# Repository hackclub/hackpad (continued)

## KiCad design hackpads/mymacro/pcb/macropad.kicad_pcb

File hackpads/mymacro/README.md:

# HackPad
## My experience
As part of **Hack Club’s HACKPAD YSWS** program, I embarked on a rewarding journey to build my own DIY macropad. This experience allowed me to explore various technical disciplines, from designing a custom **PCB in KiCAD** to **coding my very own firmware with QMK**. The most challenging aspect of the project was undoubtedly the PCB design. It required extensive research into component specifications, navigating datasheets, and ensuring that each part—switches, diodes, microcontrollers—was properly integrated into the design. The process of **placing components and routing the traces** was the most time-consuming and working through these challenges gave me a much deeper understanding of electronics design.

On the other hand, the part I enjoyed the most was **working with CAD**. With my existing CAD skills, I was able to confidently create a functional layout for the macropad’s physical structure. Translating these skills into real-world applications for a product I could use was fulfilling and rewarding. Coding the firmware was surprisingly straightforward, thanks to QMK's user-friendly environment, making the software side of things much simpler than anticipated. 
***Overall, this project was an invaluable learning experience that not only introduced me to PCB design but also allowed me to merge my existing skills with new knowledge to create something functional.***
## Bill Of Materials

    Xiao RP2040
    PCF8574 IO expander
    SSD1306 0.96 OLED
    (2) 4.7k resistor
    (16) SK6812 LED
    (16) 1N4148 diodes
    (16) Cherry MX brown switches

    (16) any keycaps at hq
    (16) Mill-Max 0305s hotswap socket
    (2) any encoder knobs at hq
    (2) EC11 encoder with click function
    
    **--> Please laser cut the plate in 3mm clear acrylic and 3D print the rest of the pieces.**

### My Model

### My schematic

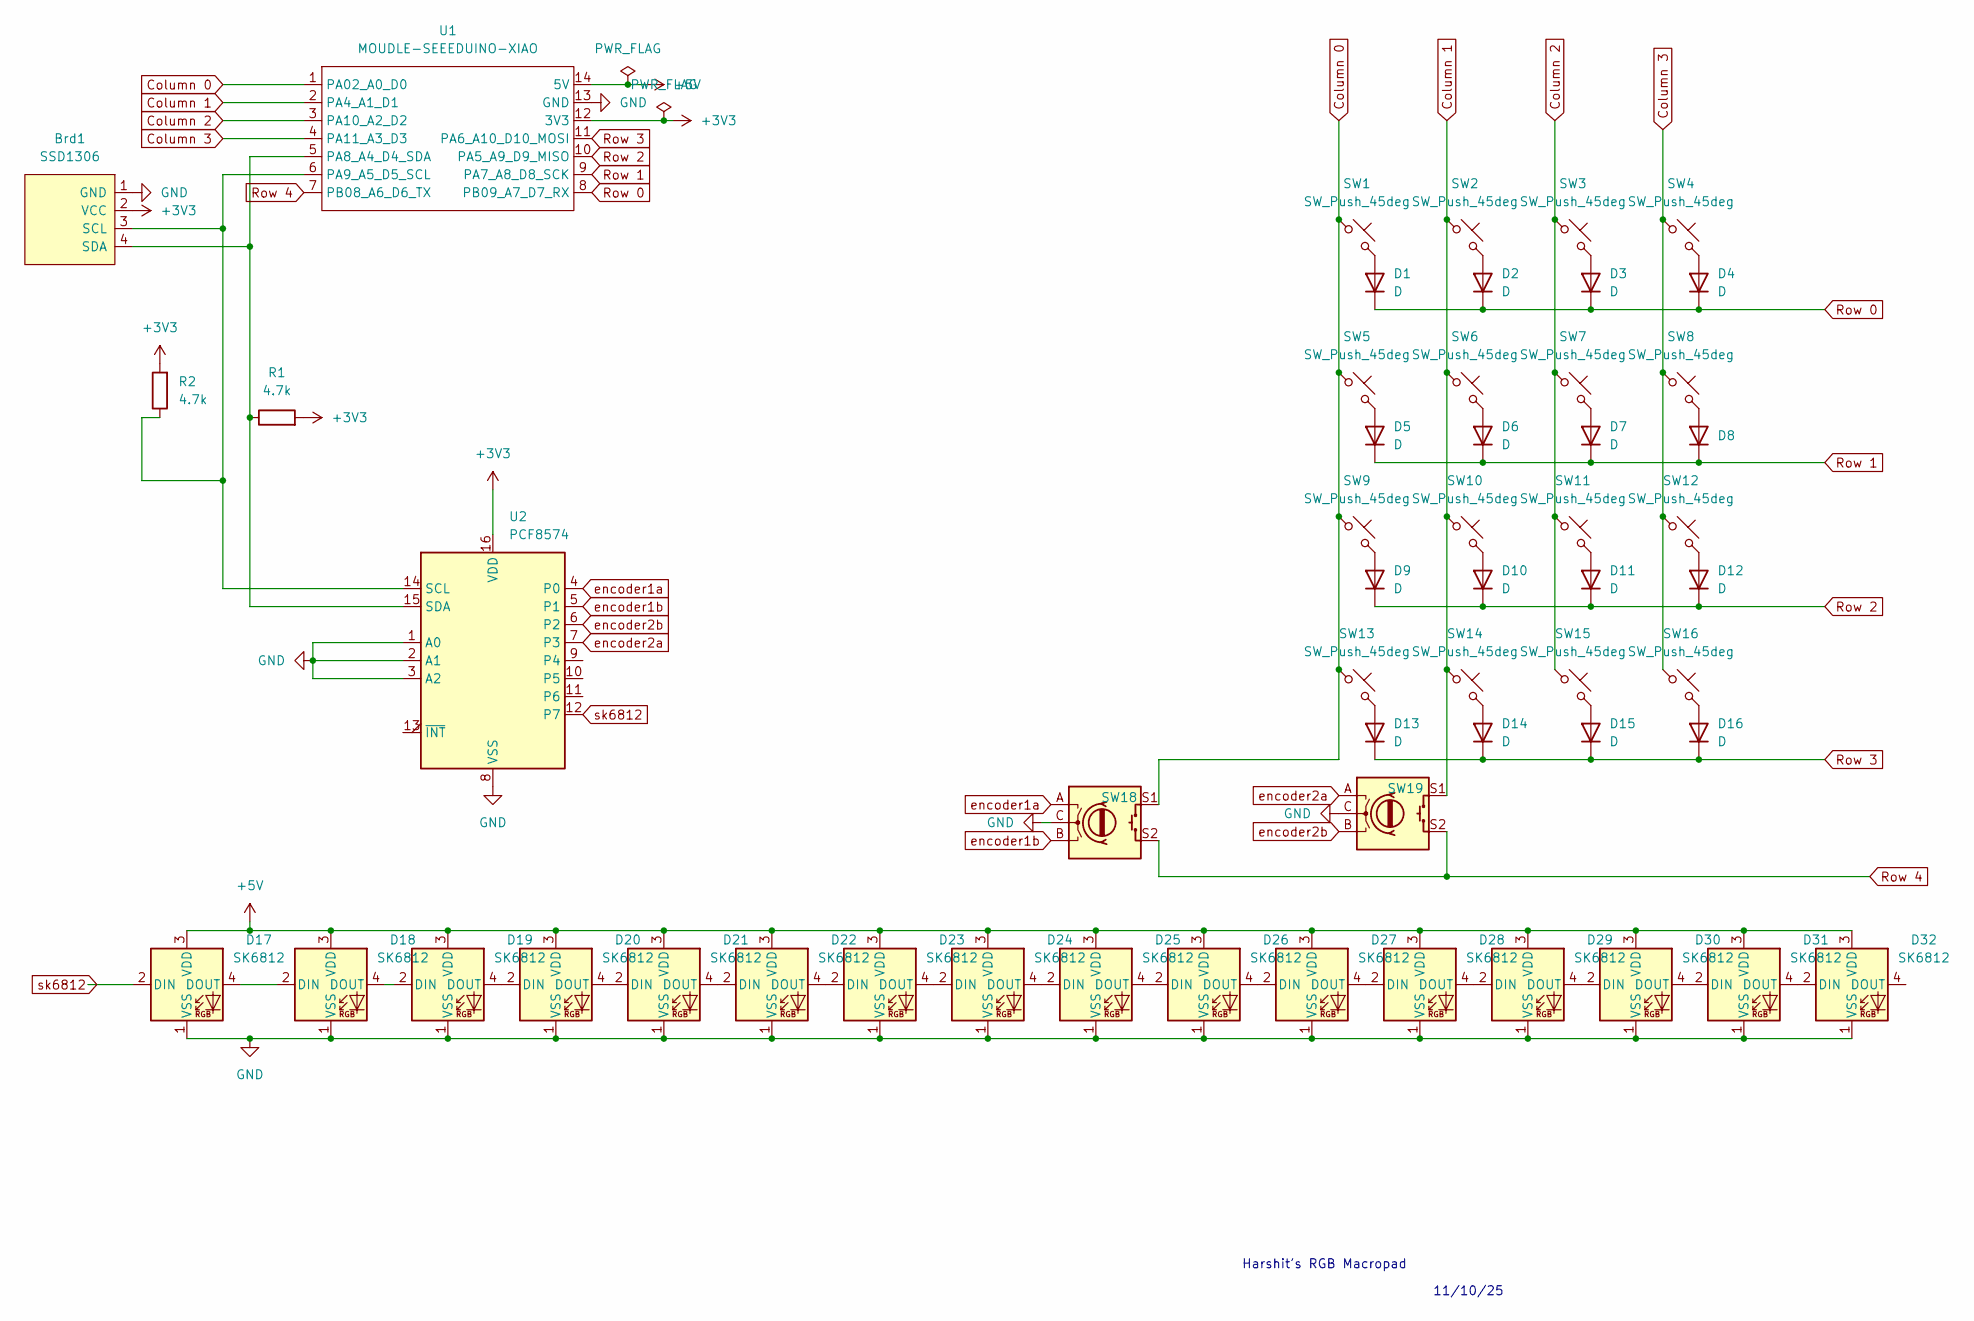
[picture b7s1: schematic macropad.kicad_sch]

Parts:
Brd1: SSD1306; 128x64OLED
D1, D2, D3, D4, D5, D6, D7, D8, D9, D10, D11, D12, D13, D14, D15, D16: D; D_DO-35_SOD27_P7.62mm_Horizontal
D17, D18, D19, D20, D21, D22, D23, D24, D25, D26, D27, D28, D29, D30, D31, D32: SK6812; LED_SK6812_PLCC4_5.0x5.0mm_P3.2mm
R1, R2: 4.7k; R_Axial_DIN0204_L3.6mm_D1.6mm_P5.08mm_Horizontal
SW1, SW2, SW3, SW4, SW5, SW6, SW7, SW8, SW9, SW10, SW11, SW12, SW13, SW14, SW15, SW16: SW_Push_45deg; SW_Cherry_MX_1.00u_PCB
SW18, SW19: RotaryEncoder_Switch; RotaryEncoder_Alps_EC11E-Switch_Vertical_H20mm
U1: MOUDLE-SEEEDUINO-XIAO; MOUDLE14P-2.54-21X17.8MM
U2: PCF8574; N16

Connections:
+3V3: Brd1.2 (VCC), R1.2, R2.2, U1.12 (3V3), U2.16 (VDD)
+5V: D17.3 (VDD), D18.3 (VDD), D19.3 (VDD), D20.3 (VDD), D21.3 (VDD), D22.3 (VDD), D23.3 (VDD), D24.3 (VDD), D25.3 (VDD), D26.3 (VDD), D27.3 (VDD), D28.3 (VDD), D29.3 (VDD), D30.3 (VDD), D31.3 (VDD), D32.3 (VDD), U1.14 (5V)
Column 0: SW1.1, SW5.1, SW9.1, SW13.1, SW18.S1, U1.1 (PA02_A0_D0)
Column 1: SW2.1, SW6.1, SW10.1, SW14.1, SW19.S1, U1.2 (PA4_A1_D1)
Column 2: SW3.1, SW7.1, SW11.1, SW15.1, U1.3 (PA10_A2_D2)
Column 3: SW4.1, SW8.1, SW12.1, SW16.1, U1.4 (PA11_A3_D3)
GND: Brd1.1 (GND), D17.1 (VSS), D18.1 (VSS), D19.1 (VSS), D20.1 (VSS), D21.1 (VSS), D22.1 (VSS), D23.1 (VSS), D24.1 (VSS), D25.1 (VSS), D26.1 (VSS), D27.1 (VSS), D28.1 (VSS), D29.1 (VSS), D30.1 (VSS), D31.1 (VSS), D32.1 (VSS), SW18.C, SW19.C, U1.13 (GND), U2.1 (A0), U2.2 (A1), U2.3 (A2), U2.8 (VSS)
unnamed: Brd1.3 (SCL), R2.1, U1.6 (PA9_A5_D5_SCL), U2.14 (SCL)
unnamed: Brd1.4 (SDA), R1.1, U1.5 (PA8_A4_D4_SDA), U2.15 (SDA)
unnamed: D1.2 (A), SW1.2
unnamed: D2.2 (A), SW2.2
unnamed: D3.2 (A), SW3.2
unnamed: D4.2 (A), SW4.2
unnamed: D5.2 (A), SW5.2
unnamed: D6.2 (A), SW6.2
unnamed: D7.2 (A), SW7.2
unnamed: D8.2 (A), SW8.2
unnamed: D9.2 (A), SW9.2
unnamed: D10.2 (A), SW10.2
unnamed: D11.2 (A), SW11.2
unnamed: D12.2 (A), SW12.2
unnamed: D13.2 (A), SW13.2
unnamed: D14.2 (A), SW14.2
unnamed: D15.2 (A), SW15.2
unnamed: D16.2 (A), SW16.2
unnamed: D17.4 (DOUT), D18.2 (DIN)
unnamed: D18.4 (DOUT), D19.2 (DIN)
unnamed: D19.4 (DOUT), D20.2 (DIN)
unnamed: D20.4 (DOUT), D21.2 (DIN)
unnamed: D21.4 (DOUT), D22.2 (DIN)
unnamed: D22.4 (DOUT), D23.2 (DIN)
unnamed: D23.4 (DOUT), D24.2 (DIN)
unnamed: D24.4 (DOUT), D25.2 (DIN)
unnamed: D25.4 (DOUT), D26.2 (DIN)
unnamed: D26.4 (DOUT), D27.2 (DIN)
unnamed: D27.4 (DOUT), D28.2 (DIN)
unnamed: D28.4 (DOUT), D29.2 (DIN)
unnamed: D29.4 (DOUT), D30.2 (DIN)
unnamed: D30.4 (DOUT), D31.2 (DIN)
unnamed: D31.4 (DOUT), D32.2 (DIN)
Row 0: D1.1 (K), D2.1 (K), D3.1 (K), D4.1 (K), U1.8 (PB09_A7_D7_RX)
Row 1: D5.1 (K), D6.1 (K), D7.1 (K), D8.1 (K), U1.9 (PA7_A8_D8_SCK)
Row 2: D9.1 (K), D10.1 (K), D11.1 (K), D12.1 (K), U1.10 (PA5_A9_D9_MISO)
Row 3: D13.1 (K), D14.1 (K), D15.1 (K), D16.1 (K), U1.11 (PA6_A10_D10_MOSI)
Row 4: SW18.S2, SW19.S2, U1.7 (PB08_A6_D6_TX)
encoder1a: SW18.A, U2.4 (P0)
encoder1b: SW18.B, U2.5 (P1)
encoder2a: SW19.A, U2.7 (P3)
encoder2b: SW19.B, U2.6 (P2)
sk6812: D17.2 (DIN), U2.12 (P7)

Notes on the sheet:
11/10/25
Harshit's RGB Macropad

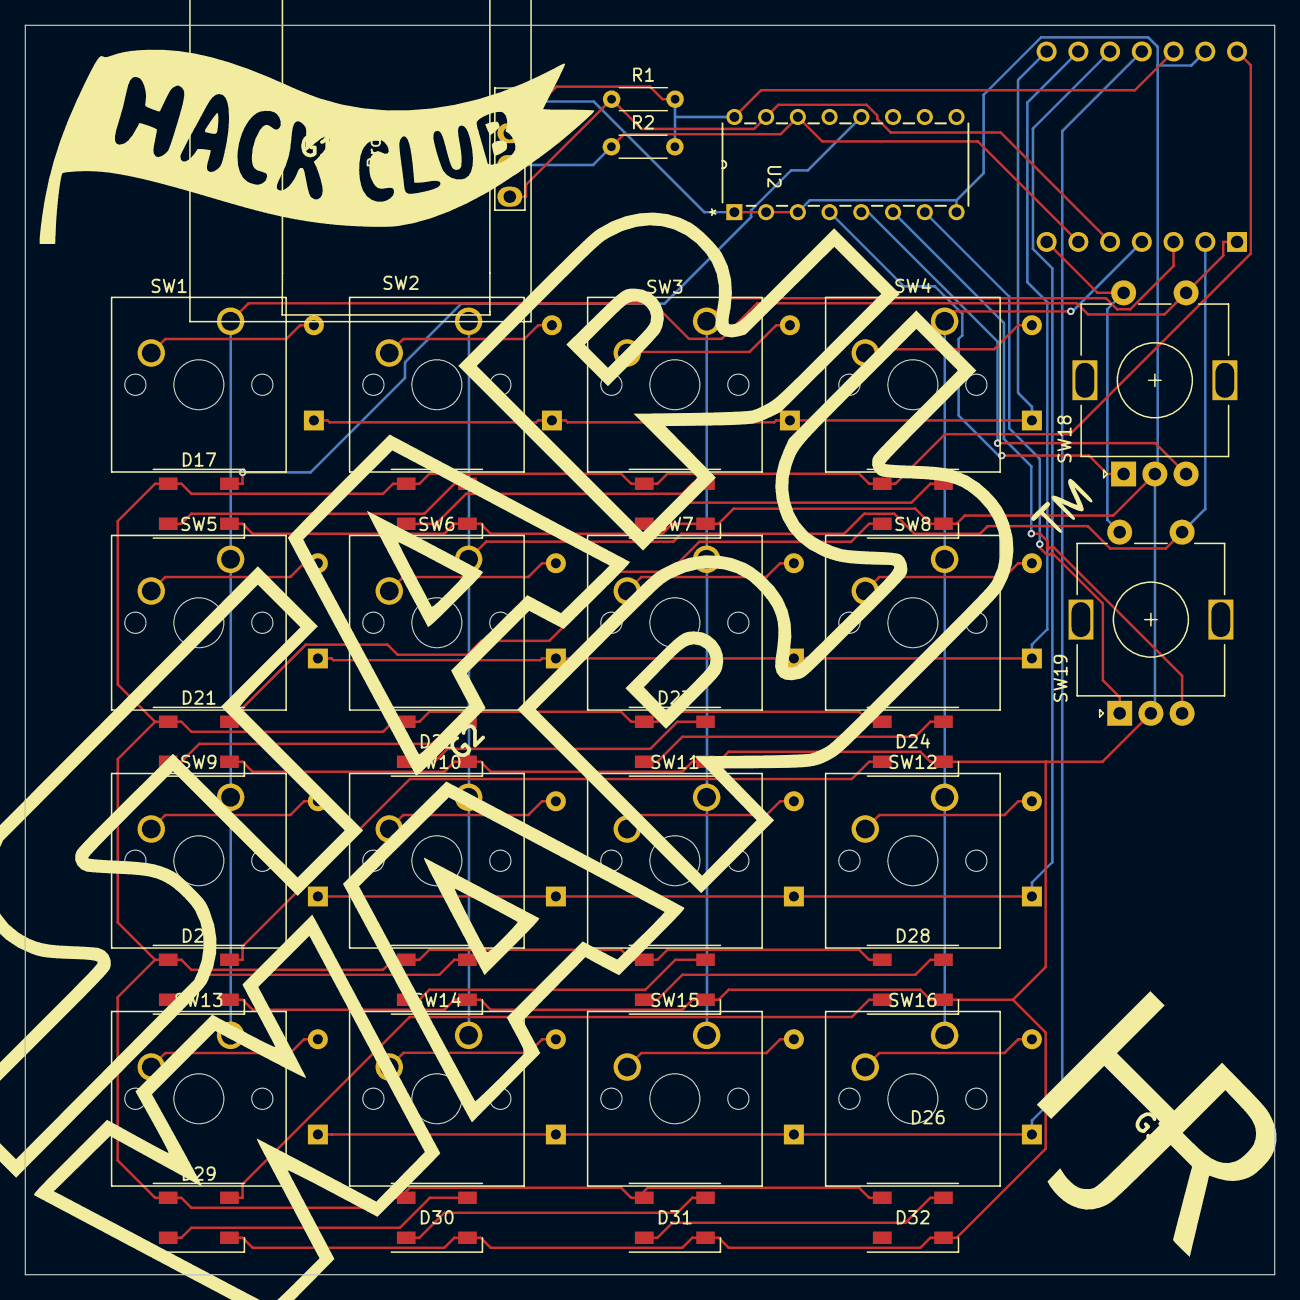
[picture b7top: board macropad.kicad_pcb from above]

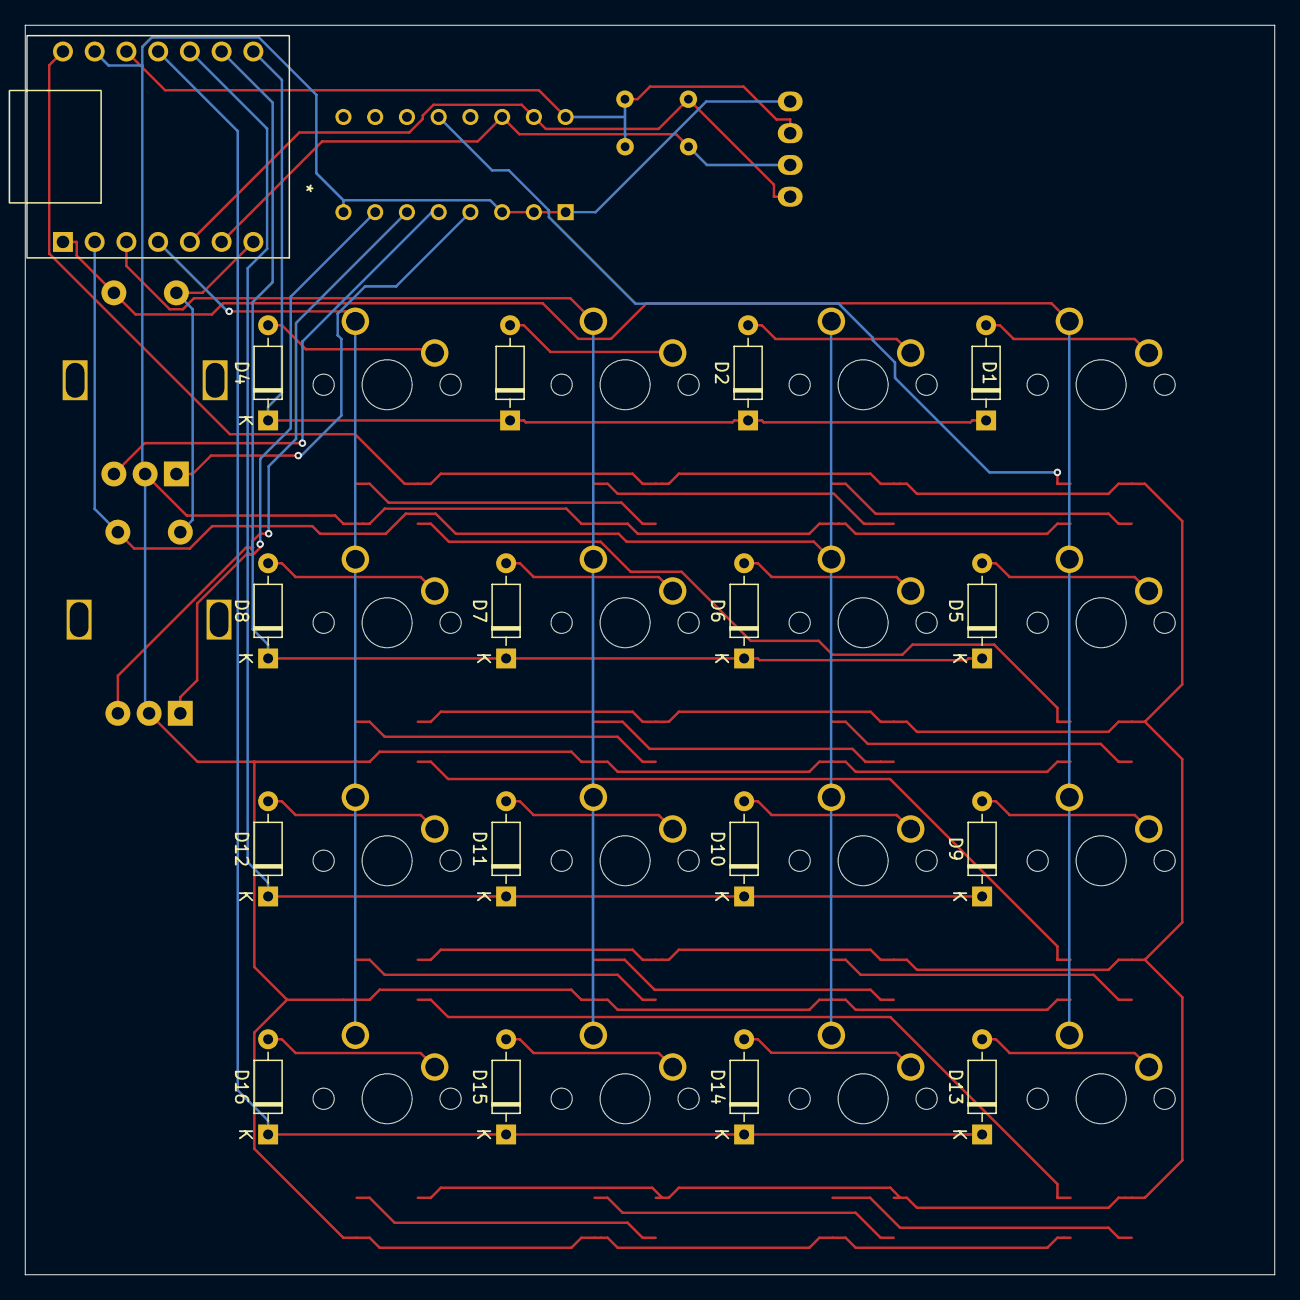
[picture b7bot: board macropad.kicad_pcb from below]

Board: 2 copper layers, 100.0 x 100.0 mm, 58 parts (17 on the bottom side), 50 nets.

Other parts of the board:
G1, G2, G3: LOGO

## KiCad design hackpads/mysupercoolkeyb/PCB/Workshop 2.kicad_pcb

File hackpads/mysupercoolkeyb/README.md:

# Bill of Materials

1. **Cherry MX Style Switches**
    - Quantity: 4

2. **PCB**
    - Quantity: 1

3. **Seeed Studio Xiao RP2040 Microcontroller**
    - Quantity: 1

## something

As I have much experience working in fusion 360, the CAD design for the case came easily to me; however working on the PCB in kicad was an entirely new experience to me, I do intend to design a split keyboard in future, and this definetly helped me get closer to that goal, funded by my dad for christmas. Working with firmware for the keyboard was also a new experience for me. Hack Club has been a really helpful in getting me out of my comfort zone, it's been a while since I've started a new project in a new software.

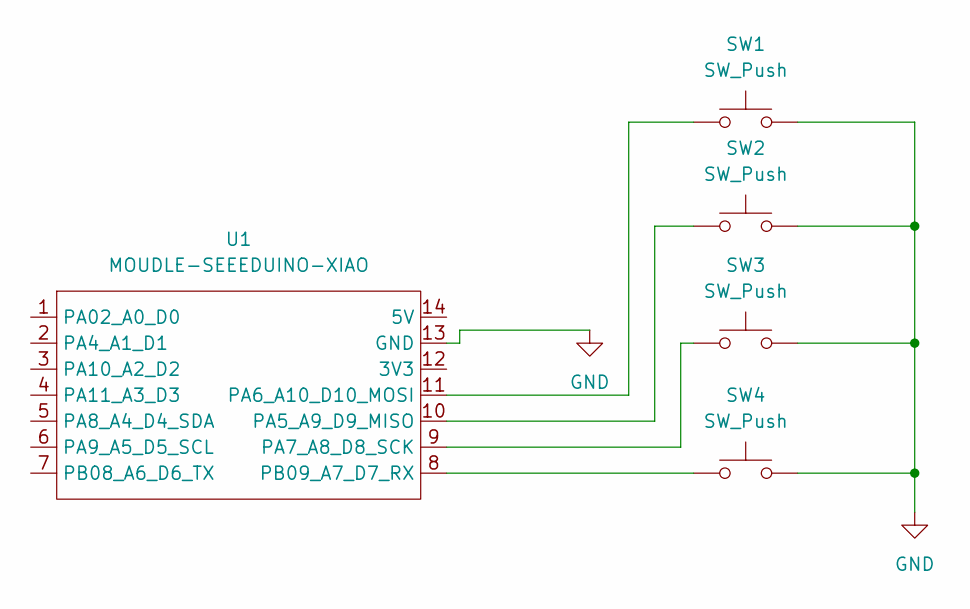
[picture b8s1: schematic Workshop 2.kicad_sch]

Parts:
SW1, SW2, SW3, SW4: SW_Push; SW_Cherry_MX_Plate_1.00u
U1: MOUDLE-SEEEDUINO-XIAO; XIAO-Generic-Hybrid-14P-2.54-21X17.8MM

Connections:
GND: SW1.2, SW2.2, SW3.2, SW4.2, U1.13 (GND)
unnamed: SW2.1, U1.10 (PA5_A9_D9_MISO)
unnamed: SW1.1, U1.11 (PA6_A10_D10_MOSI)
unnamed: SW3.1, U1.9 (PA7_A8_D8_SCK)
unnamed: SW4.1, U1.8 (PB09_A7_D7_RX)

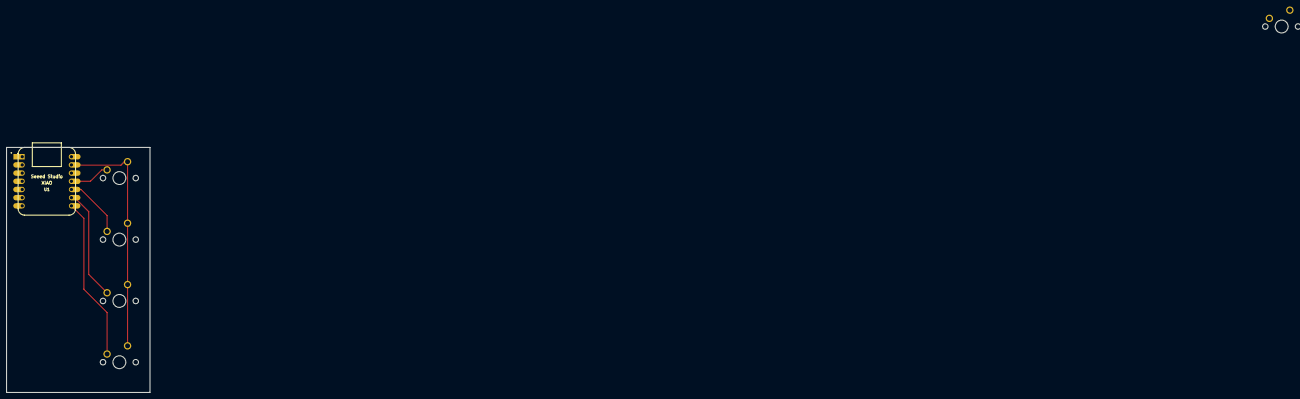
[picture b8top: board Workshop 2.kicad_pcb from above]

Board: 2 copper layers, 44.5 x 76.0 mm, 5 parts (0 on the bottom side), 5 nets.

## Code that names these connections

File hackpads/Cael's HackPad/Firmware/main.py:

import board
from kmk.modules.oled import SSD1306
from kmk.extensions import KMKeyboard
from kmk.scanners import DiodeOrientation
from kmk.keys import KC
import analogio

keyboard = KMKKeyboard()

# Matrix setup
keyboard.col_pins = [board.GPIO4, board.GPIO2, board.GPIO1]
keyboard.row_pins = [board.GPB5, board.GPB6, board.GPB7]
keyboard.diode_orientation = DiodeOrientation.COL2ROW

# Slider setup
slider1 = analogio.AnalogIn(board.GPIO26)
slider2 = analogio.AnalogIn(board.GPIO27)

# OLED setup
oled1306 = SSD1306(
    i2c_addr=0x3C, i2c_device=board.I2C(scl=board.GPIO7, sda=board.GPIO6)
)


# gets the % position of the slider
def get_slider_percent(slider):
    return int((slider.value * 100) / 65535)


# puts the slider % on the screen
def oled_update(oled):
    oled.fill()
    oled.text(f"{get_slider_percent(slider1)}%", 0, 0)
    oled.text(f"{get_slider_percent(slider2)}%", 0, 10)
    oled.show()


keyboard.modules.append(oled1306)
keyboard.keymap = [[KC.Q, KC.W, KC.E, KC.A, KC.S, KC.D, KC.Z, KC.X, KC.C]]

# once I have it physically I'm going to have the sliders adjust mic & spotify volumes respectively, and the buttons will be either for a mini keyboard or mute/unmute/play/pause hotkeys
# for now, this will just ensure that the pin layouts are working as intended and the connections are correct
# the volume control will probably need a script running in the pc itself but that's ok!

if __name__ == "__main__":
    keyboard.go()

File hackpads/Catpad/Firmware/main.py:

import board
import busio
from kmk.kmk_keyboard import KMKKeyboard
from kmk.keys import KC
from kmk.scanners import DiodeOrientation
from kmk.extensions.display import Display, TextEntry
from kmk.extensions.display.ssd1306 import SSD1306

# Define column and row pins for a 4x5 matrix
COL1 = board.D2
COL2 = board.D3
COL3 = board.D4
COL4 = board.D5
ROW1 = board.D6
ROW2 = board.D7
ROW3 = board.D8
ROW4 = board.D9
ROW5 = board.D10

# Initialize I2C bus for the displays
i2c_bus = busio.I2C(board.D4, board.D5)

# Initialize the SSD1306 displays
display_driver1 = SSD1306(
    i2c=i2c_bus,
    device_address=0x3C,  # First OLED address
)

display_driver2 = SSD1306(
    i2c=i2c_bus,
    device_address=0x3D,  # Second OLED address
)

# Create the keyboard instance
keyboard = KMKKeyboard()

# Define column and row pins
keyboard.col_pins = (COL1, COL2, COL3, COL4)
keyboard.row_pins = (ROW1, ROW2, ROW3, ROW4, ROW5)
keyboard.diode_orientation = DiodeOrientation.COL2ROW

# Set up the displays with initial text
display1 = Display(
    display=display_driver1,
    entries=[TextEntry(text='Name', x=0, y=0, y_anchor='M')],
    width=128,
    height=32,
    dim_time=10,
    dim_target=0.2,
    off_time=1200,
    brightness=1,
)

display2 = Display(
    display=display_driver2,
    entries=[TextEntry(text='WELCOME', x=0, y=0, y_anchor='M')],
    width=128,
    height=32,
    dim_time=10,
    dim_target=0.2,
    off_time=1200,
    brightness=1,
)

# Add displays to keyboard extensions
keyboard.extensions.append(display1)
keyboard.extensions.append(display2)

# Define the keymap
keyboard.keymap = [
    [KC.MPRV, KC.MNXT, KC.NO, KC.NO],  # Row 1
    [KC.NO,   KC.NO,   KC.NO, KC.NO],  # Row 2
    [KC.NO,   KC.Z,    KC.X,  KC.NO],  # Row 3
    [KC.NO,   KC.NO,   KC.NO, KC.NO],  # Row 4
    [KC.NO,   KC.NO,   KC.NO, KC.NO],  # Row 5
]

# Start the keyboard
if __name__ == '__main__':
    keyboard.go()
